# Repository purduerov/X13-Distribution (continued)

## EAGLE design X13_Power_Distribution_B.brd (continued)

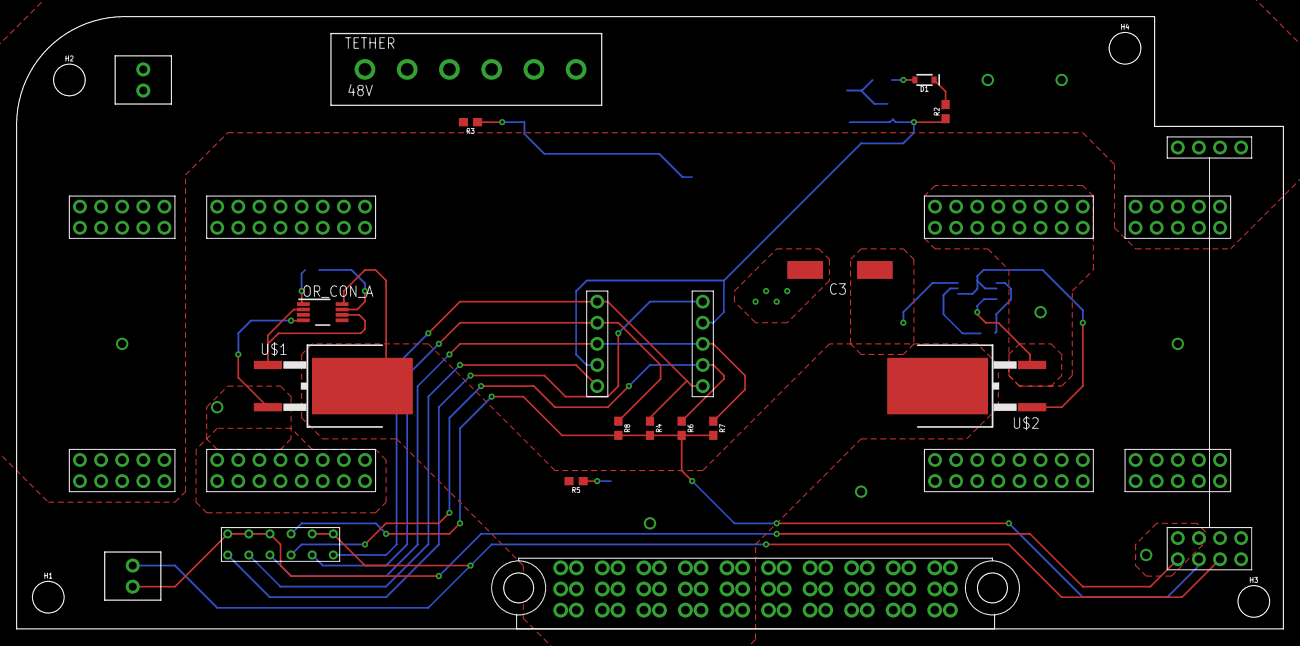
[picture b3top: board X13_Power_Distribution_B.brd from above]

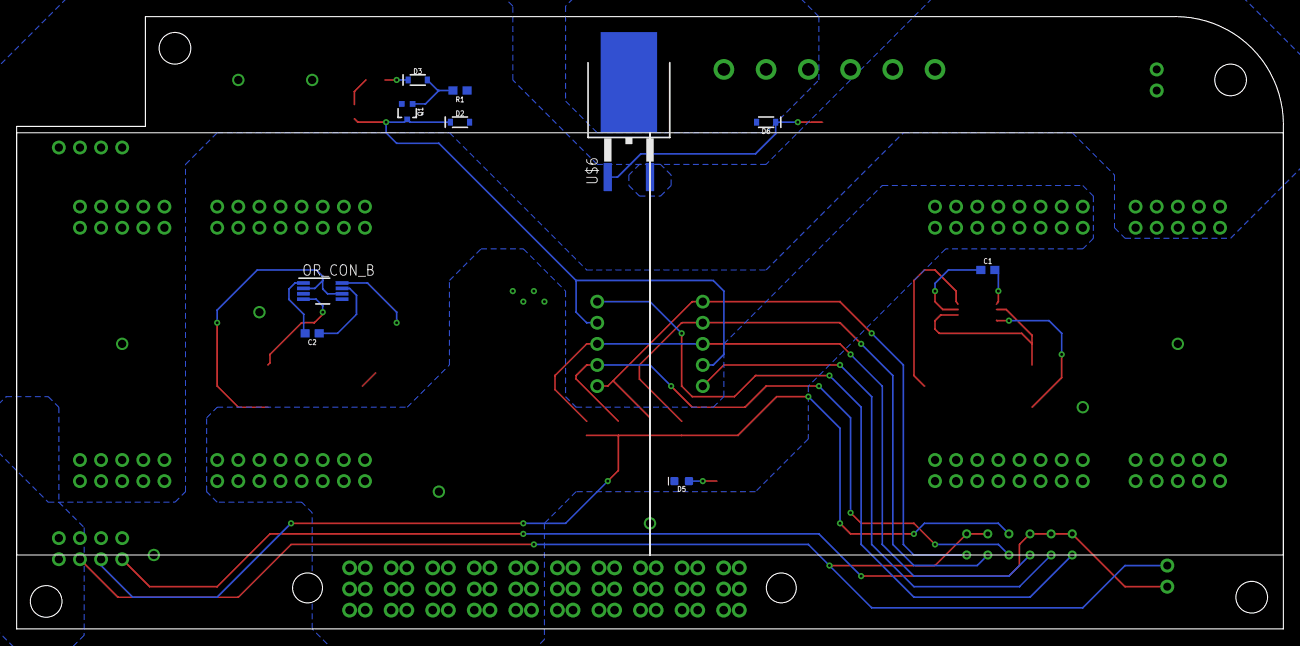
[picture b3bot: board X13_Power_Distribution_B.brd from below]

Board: 2 copper layers, 152.4 x 73.7 mm, 34 parts (10 on the bottom side), 27 nets.

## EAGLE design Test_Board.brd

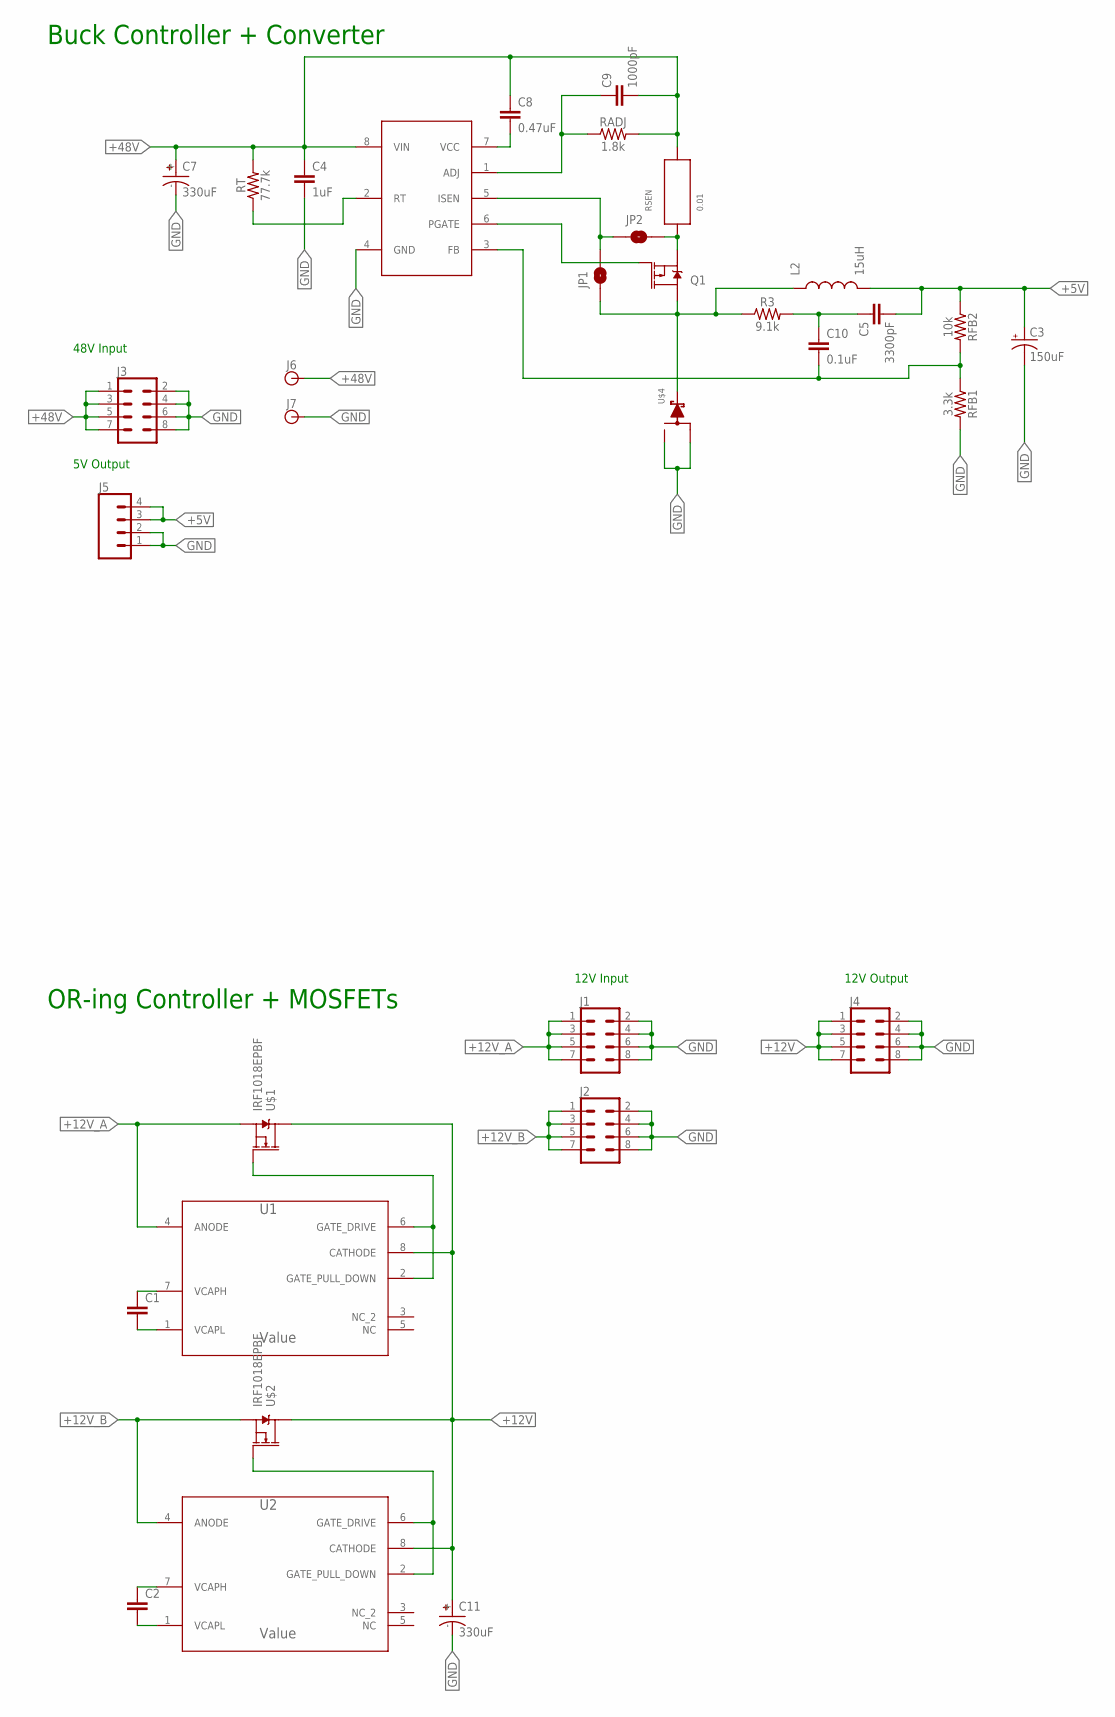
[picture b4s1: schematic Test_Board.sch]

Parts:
C1, C2: 0.1UF-0603-100V-10%; 0603
C3: 150uF; CTAN(7.30_4.30MM)
C4: 1uF; 0603
C5: 3300pF; 0603
C7, C11: 330uF; CAPAE1030X1050N
C8: 0.47uF; 0603
C9: 1000pF; 0603
C10: 0.1uF; 0603
J1, J2, J3, J4: CONN_04X2; 2X4
J5: CONN_041X04_NO_SILK; 1X04_NO_SILK
J6, J7: BANANA_CONN
JP1, JP2: JUMPER-SMT_2_NO_NO-SILK; SMT-JUMPER_2_NO_NO-SILK
L2: 15uH; HCMA1305
Q1: MOSFET_PCH-NDS8434; SO08
R3: 9.1k; 0603
RADJ: 1.8k; 0603
RFB1: 3.3k; 0603
RFB2: 10k; 0603
RSEN: 0.01; CSS2H-2512
RT: 77.7k; 0603
U1, U2: Value; DGK0008A_M
U$1, U$2: IRF1018EPBF; TO263
U$3: LM5085
U$4: SWITCHMODE_SCHOTTKY; DPAK-3

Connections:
+5V: C3.+, C5.2, J5.3, J5.4, L2.2, RFB2.1
+12V: C11.+, J4.1, J4.3, J4.5, J4.7, U1.8 (CATHODE), U2.8 (CATHODE), U$1.3 (D), U$2.3 (D)
+12V_A: J1.1, J1.3, J1.5, J1.7, U1.4 (ANODE), U$1.2 (S)
+12V_B: J2.1, J2.3, J2.5, J2.7, U2.4 (ANODE), U$2.2 (S)
+48V: C4.1, C7.+, C8.1, C9.2, J3.1, J3.3, J3.5, J3.7, J6.P$1, RADJ.2, RSEN.2, RT.2, U$3.8 (VIN)
FB: C10.2, RFB1.1, RFB2.2, U$3.3 (FB)
GATE: Q1.4 (G), U$3.6 (PGATE)
GND: C3.-, C4.2, C7.-, C11.-, J1.2, J1.4, J1.6, J1.8, J2.2, J2.4, J2.6, J2.8, J3.2, J3.4, J3.6, J3.8, J4.2, J4.4, J4.6, J4.8, J5.1, J5.2, J7.P$1, RFB1.2, U$3.4 (GND), U$4.P$1, U$4.P$3
ISEN: JP1.2, JP2.1, U$3.5 (ISEN)
unnamed: C9.1, RADJ.1, U$3.1 (ADJ)
unnamed: C2.1, U2.7 (VCAPH)
unnamed: C2.2, U2.1 (VCAPL)
unnamed: C1.2, U1.1 (VCAPL)
unnamed: C1.1, U1.7 (VCAPH)
unnamed: U1.2 (GATE_PULL_DOWN), U1.6 (GATE_DRIVE), U$1.1 (G)
unnamed: C5.1, C10.1, R3.2
unnamed: U2.2 (GATE_PULL_DOWN), U2.6 (GATE_DRIVE), U$2.1 (G)
unnamed: JP2.2, Q1.1 (S), Q1.2 (S), Q1.3 (S), RSEN.1
RT: RT.1, U$3.2 (RT)
SW: JP1.1, L2.1, Q1.5 (D), Q1.6 (D), Q1.7 (D), Q1.8 (D), R3.1, U$4.P$4
VCC: C8.2, U$3.7 (VCC)

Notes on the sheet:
OR-ing Controller + MOSFETs
Buck Controller + Converter
48V Input
5V Output
12V Input
12V Output

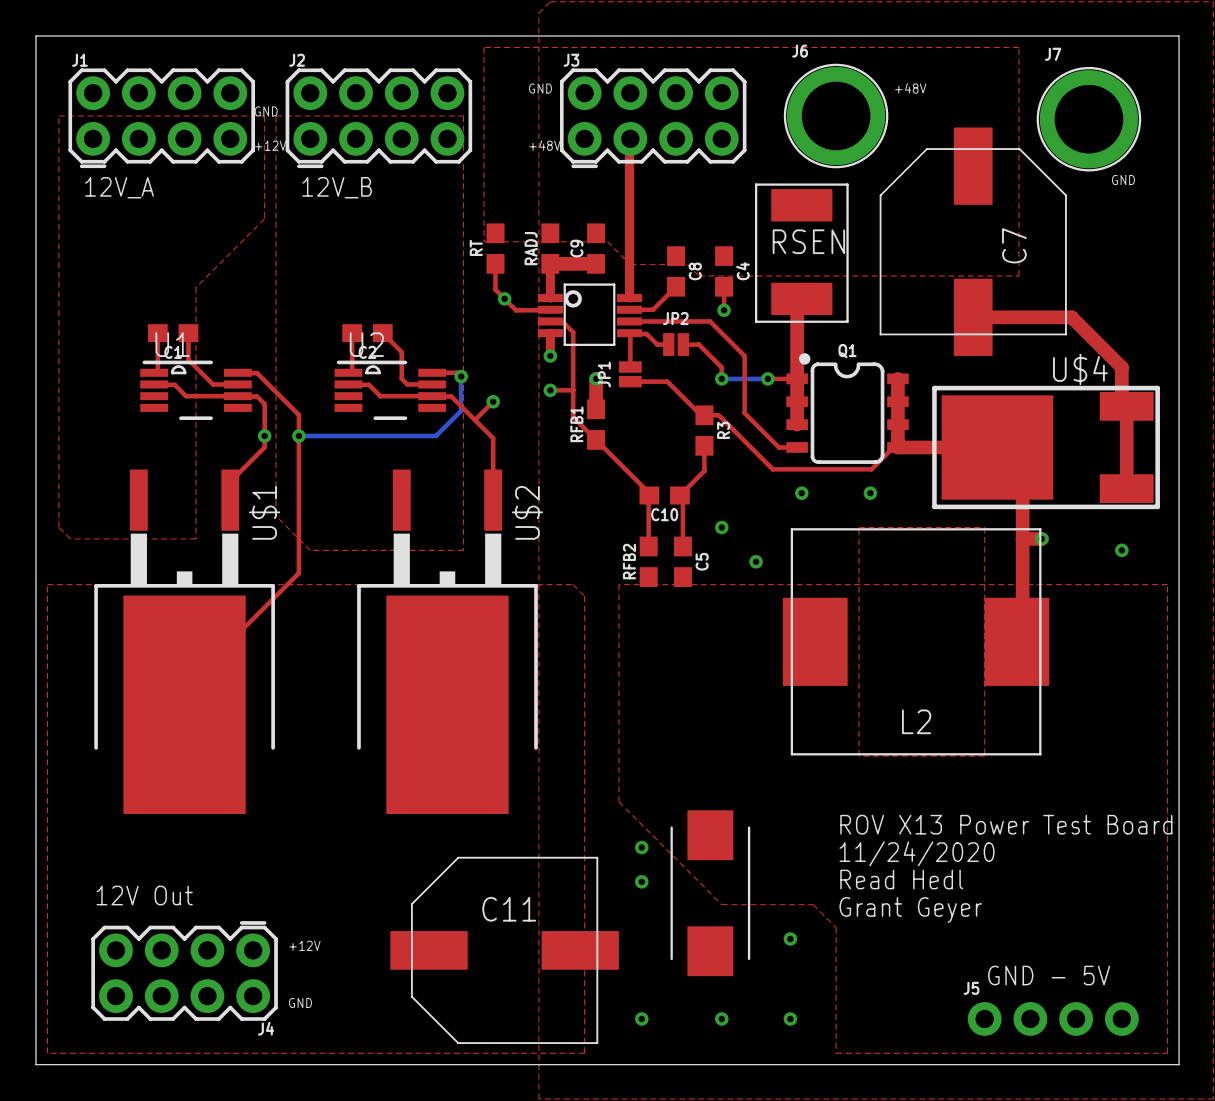
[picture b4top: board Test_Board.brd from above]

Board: 2 copper layers, 63.5 x 57.1 mm, 33 parts (0 on the bottom side), 21 nets.

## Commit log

2020-09-18 setup of repo
2020-10-07 made da schematic
2020-10-10 Made some slight changes
2020-10-14 goodbye microcontroller
2020-10-17 Added the diodes :))
2020-10-17 Starting on connectors
2020-10-21 Added placeholders
2020-10-21 removed the custom conversion connector
2020-10-23 ready for design review 1 :3
2020-10-25 center frame in schematic and add board dimension
2020-10-29 am sleepy
2020-10-31 It's pretty now :3
2020-10-31 moved the bus connectors a bit
2020-11-07 layout!
2020-11-14 Design review time
2020-11-14 cap placeholders fixed
2020-11-19 started test board, adjusting Buck controller
2020-11-21 2020/11/21
2020-11-21 initial placements done
2020-11-22 finished routing, but dont have senior design DRC on my PC to check
2020-11-22 finished routing. Need DRC
2020-11-22 added sense resistor
2020-11-22 rerouted buck converter, trying to mitigate distance and also follow the recommended layout
2020-11-24 adjusted buck controller
2020-11-24 Added U-shape for external wire
2020-11-24 bigger U and a few labels. inductor pour cutout
2020-11-24 couple silkscreen changes to order
2020-12-02 routed :)
2020-12-04 Routed with custom connectors
2020-12-05 Fixed some DRC errors
2020-12-05 B is a second version that uses the Version B connectors
2020-12-21 Version C! Uses connector C!
2020-12-22 5V and 3.3V traces are wider now
2020-12-23 Moved ON/OFF, moved a diode
2020-12-23 Two LEDs where once was one
2020-12-23 Some tweaks and labeling
2020-12-26 Moved 5V Ethernet, added some cutouts
2021-01-03 Jan 2nd Tweaks
2021-01-03 Moved capacitor over a bit more
2021-01-04 Added LM5050, tweaks
2021-01-04 More tweaks
2021-01-06 Version D :/
2021-01-06 Version D2 -_-
2021-01-06 Uses brick connector vD2
2021-01-06 Brick Connector D2
2021-01-07 Tweaks
2021-01-11 Exports and cleaning up git for ordering
2021-01-11 playing with 3d package generator in eagle
2021-01-20 Fix misprint in schematic
2021-03-15 Made some slight changes to thermals
2021-03-18 Some more edits
2021-03-20 Made some more lil tweaks
2021-04-05 Lower on/off threshold, remove old unused or-ing controller, try new 12V on LED circuit
2021-04-17 Add solder jumper to short on/off and diode to latch voltage
2021-04-19 Add diode to on/off to discharge gate when power supply hits 0
